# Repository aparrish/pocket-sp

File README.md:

# Pocket SP

By [Allison Parrish](https://www.decontextualize.com/)

These are the source files for the [Pocket
SP](https://posts.decontextualize.com/pocket-sp/), a Game Boy Pocket mod I made
in the summer of 2022. Here's a description of the directories in this
repository and what they contain:

* `boards`: KiCad source files for the flex PCB connector boards
* `model`: FreeCAD source files for the shell
* `stl`: Exported STL files for the various parts of the shell

You can get the flex PCB boards directly from [OSH
Park](https://oshpark.com/shared_projects/3J882cTI). (Make sure to order them
as flex PCBs, not regular PCBs!) For the shell, you'll need to download the STL
files from this repository (or export them from the FreeCAD file) and then
print them on your own 3D printer, or send them to the fabricator of your
choice. I recommend ordering an SLA resin print from
[PCBWay](https://pcbway.com/) or [JLCPCB](https://jlcpcb.com/).

Note that there is a lot more to this build than just the shell and the PCBs!
Consult the "How you can do it" section of [my
write-up](http://posts.decontextualize.com/pocket-sp/) for more information.

## License

These files are licensed as [CC
BY-NC-SA](https://creativecommons.org/licenses/by-nc-sa/4.0/). That means that
you can share and adapt the work, as long as you give appropriate credit and
release your modifications under the same license as the original. You may not
use the files in this repository for commercial purposes.

I'm happy to consider releasing the files under a different license to
individuals, depending on what they've got in mind. Get in touch with me and we
can chat!

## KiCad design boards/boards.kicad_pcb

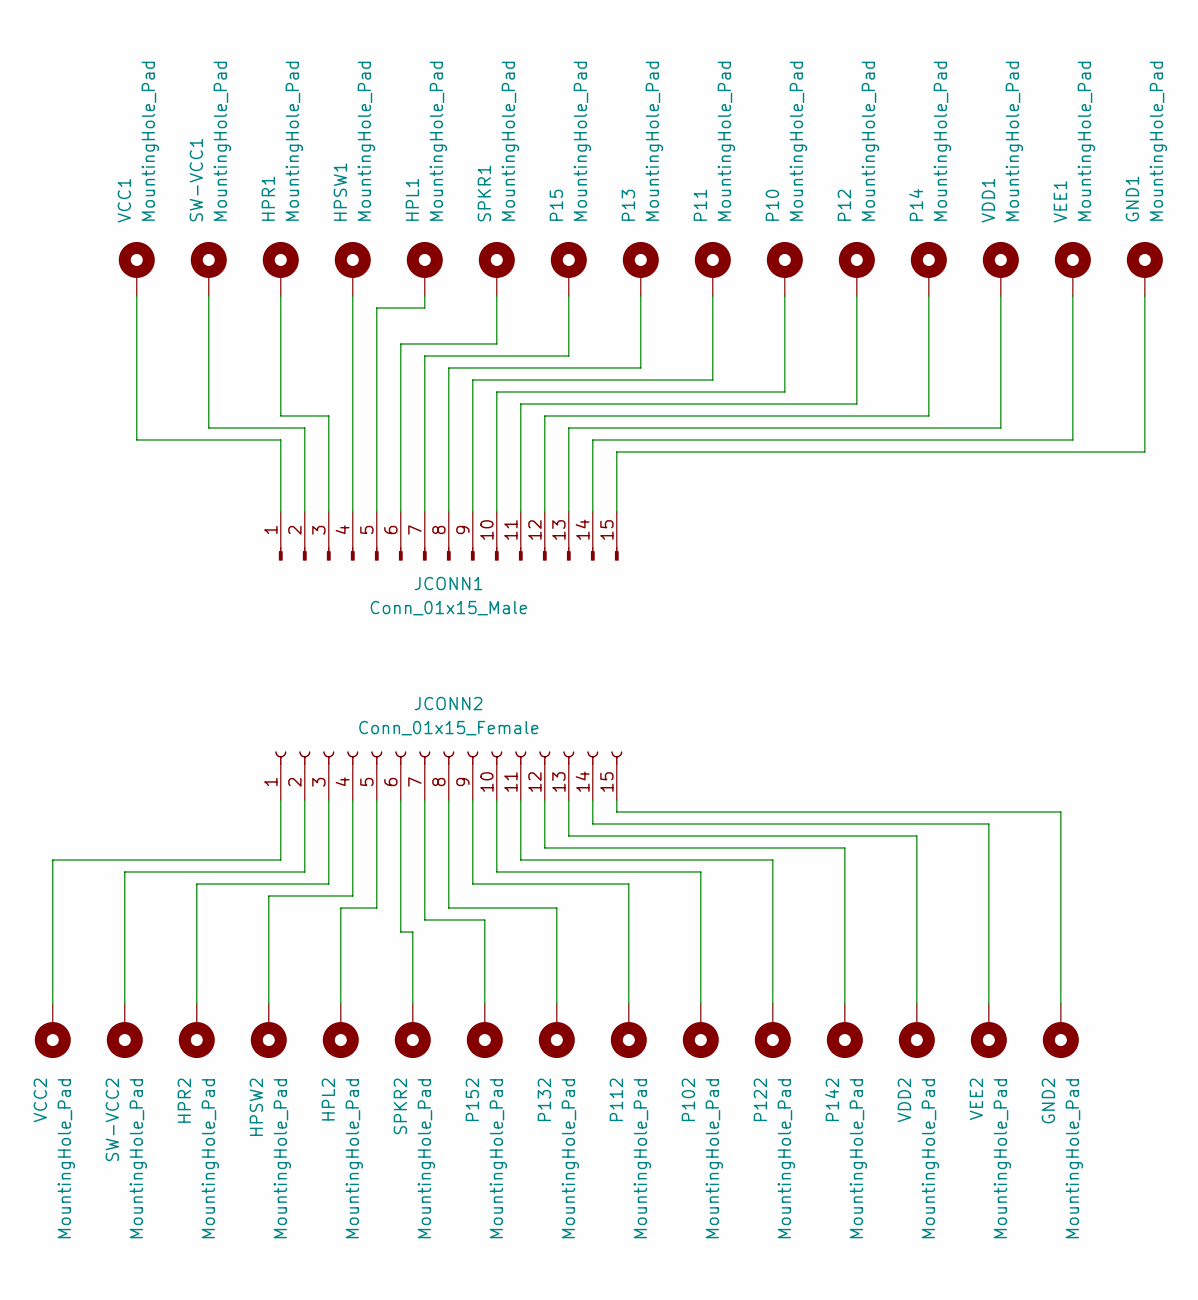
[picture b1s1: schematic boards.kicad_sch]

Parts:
GND1: MountingHole_Pad; ground solder
GND2: MountingHole_Pad; solder-to-via
HPL1, HPL2: MountingHole_Pad; solder-to-via
HPR1, HPR2: MountingHole_Pad; solder-to-via
HPSW1: MountingHole_Pad; solder-to-via
HPSW2: MountingHole_Pad; TestPoint_Pad_D1.5mm
JCONN1: Conn_01x15_Male; 0.5 pitch edge
JCONN2: Conn_01x15_Female; Hirose_FH12-15S-0.5SH_1x15-1MP_P0.50mm_Horizontal
P10, P11, P12, P13, P14, P15, P102, P112, P122, P132, P142, P152: MountingHole_Pad; solder-to-via
SPKR1: MountingHole_Pad; solder-to-via
SPKR2: MountingHole_Pad; TestPoint_Pad_D1.5mm
SW-VCC1, SW-VCC2: MountingHole_Pad; TestPoint_Pad_D1.5mm
VCC1, VCC2: MountingHole_Pad; TestPoint_Pad_D1.5mm
VDD1, VDD2: MountingHole_Pad; solder-to-via
VEE1, VEE2: MountingHole_Pad; solder-to-via

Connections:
unnamed: GND1.1, JCONN1.15
unnamed: HPL1.1, JCONN1.5
unnamed: HPR1.1, JCONN1.3
unnamed: HPSW1.1, JCONN1.4
unnamed: JCONN1.1, VCC1.1
unnamed: JCONN1.2, SW-VCC1.1
unnamed: JCONN1.6, SPKR1.1
unnamed: JCONN1.7, P15.1
unnamed: JCONN1.8, P13.1
unnamed: JCONN1.9, P11.1
unnamed: JCONN1.10, P10.1
unnamed: JCONN1.11, P12.1
unnamed: JCONN1.12, P14.1
unnamed: JCONN1.13, VDD1.1
unnamed: JCONN1.14, VEE1.1
unnamed: JCONN2.1, VCC2.1
unnamed: JCONN2.2, SW-VCC2.1
unnamed: HPR2.1, JCONN2.3
unnamed: HPSW2.1, JCONN2.4
unnamed: HPL2.1, JCONN2.5
unnamed: JCONN2.6, SPKR2.1
unnamed: JCONN2.7, P152.1
unnamed: JCONN2.8, P132.1
unnamed: JCONN2.9, P112.1
unnamed: JCONN2.10, P102.1
unnamed: JCONN2.11, P122.1
unnamed: JCONN2.12, P142.1
unnamed: JCONN2.13, VDD2.1
unnamed: JCONN2.14, VEE2.1
unnamed: GND2.1, JCONN2.15

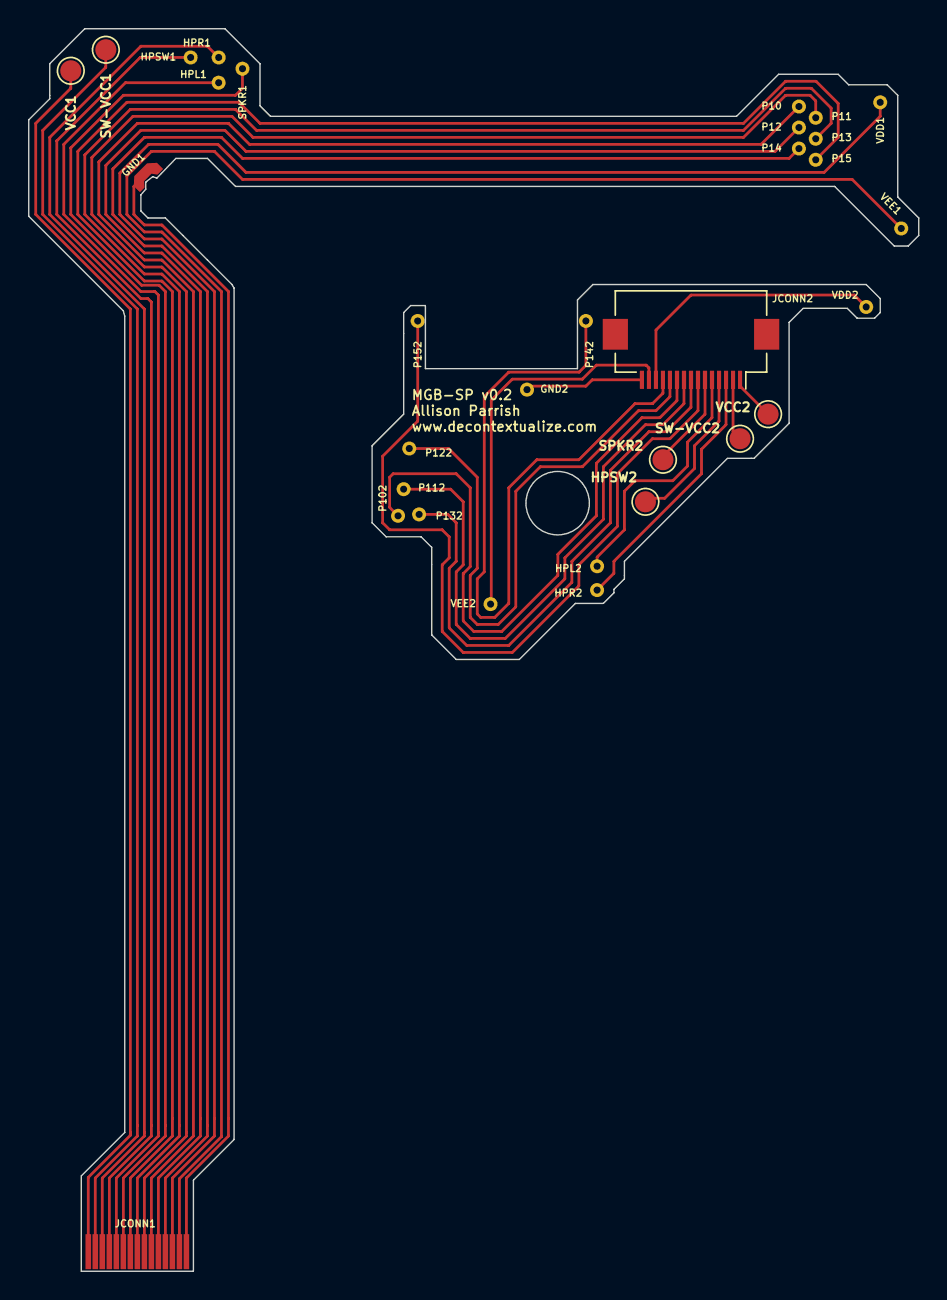
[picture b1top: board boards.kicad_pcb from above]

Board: 2 copper layers, 63.5 x 88.7 mm, 32 parts (0 on the bottom side), 30 nets.

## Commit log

2022-11-03 initial commit!
2022-11-03 forgot to remove old version
2022-11-03 typo
